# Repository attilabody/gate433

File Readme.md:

# Shared parking space access controller

## Features

Gate433 uses cheap, standard (and insecure) gate opener remotes operating on 433 MHz to control entry and exit of vehicles allowed to acces the parking area.

Each gate opener supposed to be assigned to one vehicle and has unique code. The main purpose of it is to make unfair usage of the parking as inconvinient as possible using commodity gate opener remotes.

Features list:

* 1024 possible remote codes
* Position of each vehicle (inside, outside, unknown) is remembered. Gate opening will be denied for unexpected movements (e.g vehicle which is already inside tries to enter again)
* Access time limits by direction can be set independently for any vehicle (e.g can enter Monday to Friday from 08:30 to 17:00, can leave Monday to Friday from 08:30 to 17:30)
* Vehicle database snd device configuration stored in EEPROM
* Log stored on SD card
* Database changes can be imported from SD card
* Exceptional days (e.g. National holydays) database on SD card
* Automatic DST handling
* Simple command line interpreter on serial for database manipulation, date/time setting, log manipulation and temperature query

## Hardware

There are two versions of the hardware: Original version used Arduino Nano as central component. It is obsoleted by the newer version based on a popular STM32F103C8T6 based minimal board widely known as BluePill. It's actually cheaper on eBay or Aliexpress than the total cost of the components it contains.

Both versions ar using two inputs (usually coming from inductive loop detectors) in addition to the RF signal to decide if a vehicke intends to enter or exit. A pair of tricolor traffic lights provide feedback for drivers.

Both versions have 6 opto-isolated open drain output for 12V LED traffic lights,one opto-isolated open collector output for gate opening and two opto-isolated input for inductive loop detectors.

Second iteration have three extra features compared to the first:

* WiFi to serial bridge for wireless communication
* Rotary encoder driven simpe user interface (yet to be implemented in the firmware)
* 3D printable case modelled in FreeCAD

Prototype of STM32 based version

## Firmware

Arduino Nano based firware was built on Arduino framework using Sloeber Arduino IDE. Source files persist in folders named "gatekeeper", "common" and "libs".  
STM32 version is completely separated as it is based on STM32Cube framework. STM32 sources are placed in "gatekeeper-stm32" and "stm32goodies" folder.

## Schematics and PCB

Arduino based first version hardware developed using proprietrary Eagle free version, and obsoleted by STM32 version but schematics of the [mainboard](docs/V1_mainboard.pdf) and the [IO panel](docs/V1_extio.pdf) are still available for reference.

As mentioned above, hardware of STM32 version designed using KiCAD. The complete EDA project is available in the hardware/STM32 folder. Here are the [schematics](docs/bluepill.pdf) in PDF for easier access.

PCB design for STM32 bsed version

Assembled STM32 panel with modules installed

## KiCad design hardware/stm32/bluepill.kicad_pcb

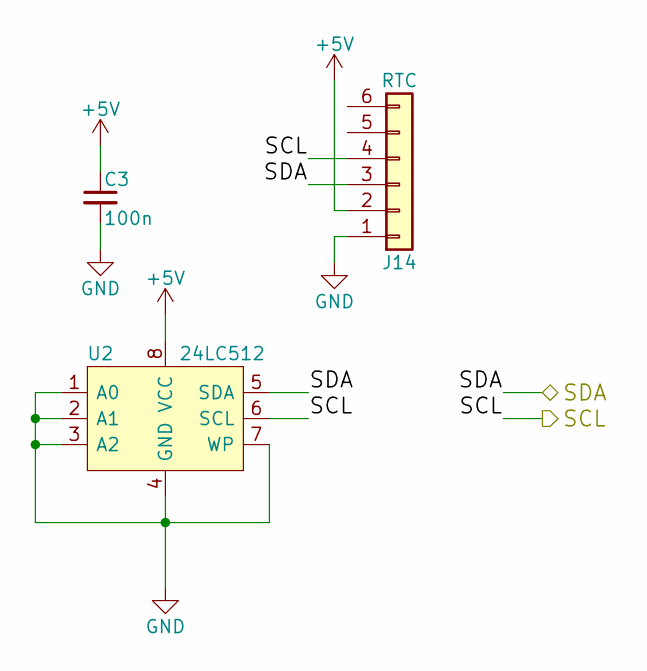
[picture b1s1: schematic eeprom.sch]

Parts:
C3: 100n; C_0805
J14: RTC; Pin_Header_Straight_1x06_Pitch2.54mm
U2: 24LC512; DIP-8_W7.62mm_LongPads

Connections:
+5V: C3.1, J14.2, U2.8 (VCC); also elsewhere on the board
/EEPROM/SCL: J14.4, U2.6 (SCL); also elsewhere on the board
/EEPROM/SDA: J14.3, U2.5 (SDA); also elsewhere on the board
GND: C3.2, J14.1, U2.1 (A0), U2.2 (A1), U2.3 (A2), U2.4 (GND), U2.7 (WP); also elsewhere on the board

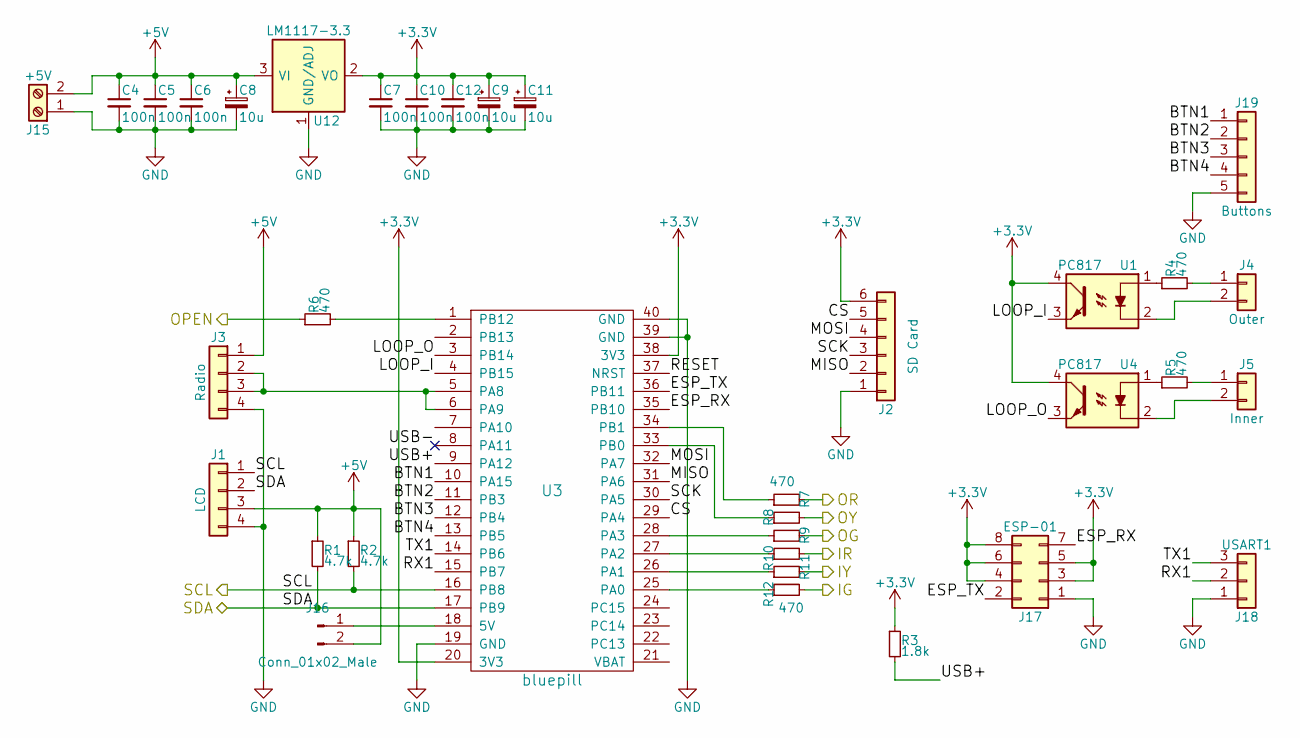
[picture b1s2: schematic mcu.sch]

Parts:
C4, C5, C6, C7, C10, C12: 100n; C_0805
C8, C9, C11: 10u; CP_Tantalum_Case-A_EIA-3216-18_Reflow
J1: LCD; Pin_Header_Straight_1x04_Pitch2.54mm
J2: SD Card; Pin_Header_Straight_1x06_Pitch2.54mm
J3: Radio; Pin_Header_Straight_1x04_Pitch2.54mm
J4: Outer; Pin_Header_Straight_1x02_Pitch2.54mm
J5: Inner; Pin_Header_Straight_1x02_Pitch2.54mm
J15: +5V; TerminalBlock_bornier-2_P5.08mm
J16: Conn_01x02_Male; Pin_Header_Straight_1x02_Pitch2.54mm
J17: ESP-01; Socket_Strip_Straight_2x04_Pitch2.54mm
J18: USART1; Pin_Header_Straight_1x03_Pitch2.54mm
J19: Buttons; Pin_Header_Straight_1x05_Pitch2.54mm
R1, R2: 4.7k; R_0603_HandSoldering
R3: 1.8k; R_0603_HandSoldering
R4, R5, R6, R7, R8, R9, R10, R11, R12: 470; R_0603_HandSoldering
U1, U4: PC817; DIP-4_W7.62mm_LongPads
U3: bluepill
U12: LM1117-3.3; SOT-223

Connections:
+3V3: C7.1, C9.1, C10.1, C11.1, C12.1, J2.6, J17.3, J17.4, J17.5, J17.6, J17.8, R3.1, U1.4, U3.20 (3V3), U3.38 (3V3), U4.4, U12.2 (VO), U12.4 (VO); also elsewhere on the board
+5V: C4.1, C5.1, C6.1, C8.1, J1.3, J3.1, J15.2, J16.2, R1.1, R2.1, U12.3 (VI); also elsewhere on the board
/EEPROM/SCL: J1.1, R2.2, U3.16 (PB8); also elsewhere on the board
/EEPROM/SDA: J1.2, R1.2, U3.17 (PB9); also elsewhere on the board
/MCU/BTN1: J19.1, U3.10 (PA15)
/MCU/BTN2: J19.2, U3.11 (PB3)
/MCU/BTN3: J19.3, U3.12 (PB4)
/MCU/BTN4: J19.4, U3.13 (PB5)
/MCU/CS: J2.5, U3.29 (PA4)
/MCU/ESP_RX: J17.7, U3.35 (PB10)
/MCU/ESP_TX: J17.2, U3.36 (PB11)
/MCU/IG: R12.2; also elsewhere on the board
/MCU/IR: R10.2; also elsewhere on the board
/MCU/IY: R11.2; also elsewhere on the board
/MCU/LOOP_I: U1.3, U3.4 (PB15)
/MCU/LOOP_O: U3.3 (PB14), U4.3
/MCU/MISO: J2.2, U3.31 (PA6)
/MCU/MOSI: J2.4, U3.32 (PA7)
/MCU/OG: R9.2; also elsewhere on the board
/MCU/OPEN: R6.1; also elsewhere on the board
/MCU/OR: R7.2; also elsewhere on the board
/MCU/OY: R8.2; also elsewhere on the board
/MCU/RX1: J18.2, U3.15 (PB7)
/MCU/SCK: J2.3, U3.30 (PA5)
/MCU/TX1: J18.3, U3.14 (PB6)
/MCU/USB+: R3.2, U3.9 (PA12)
GND: C4.2, C5.2, C6.2, C7.2, C8.2, C9.2, C10.2, C11.2, C12.2, J1.4, J2.1, J3.4, J15.1, J17.1, J18.1, J19.5, U3.19 (GND), U3.39 (GND), U3.40 (GND), U12.1 (GND/ADJ); also elsewhere on the board
unnamed: J3.2, J3.3, U3.5 (PA8), U3.6 (PA9)
unnamed: J4.1, R4.2
unnamed: J4.2, U1.2
unnamed: J5.1, R5.2
unnamed: J5.2, U4.2
unnamed: J16.1, U3.18 (5V)
unnamed: R4.1, U1.1
unnamed: R5.1, U4.1
unnamed: R6.2, U3.1 (PB12)
unnamed: R7.1, U3.34 (PB1)
unnamed: R8.1, U3.33 (PB0)
unnamed: R9.1, U3.28 (PA3)
unnamed: R10.1, U3.27 (PA2)
unnamed: R11.1, U3.26 (PA1)
unnamed: R12.1, U3.25 (PA0)

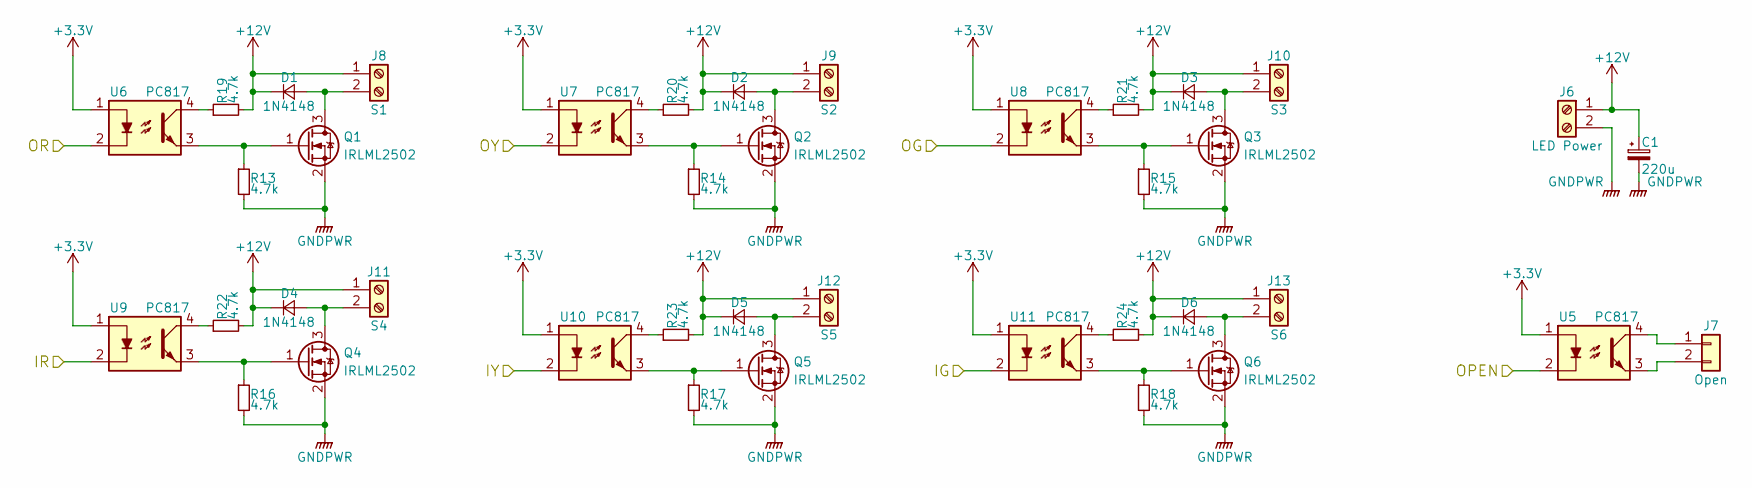
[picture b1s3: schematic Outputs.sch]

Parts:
C1: 220u; CP_Radial_D10.0mm_P3.50mm
D1, D2, D3, D4, D5, D6: 1N4148; D_MiniMELF
J6: LED Power; TerminalBlock_bornier-2_P5.08mm
J7: Open; JST_EH_B02B-EH-A_02x2.50mm_Straight
J8: S1; TerminalBlock_bornier-2_P5.08mm
J9: S2; TerminalBlock_bornier-2_P5.08mm
J10: S3; TerminalBlock_bornier-2_P5.08mm
J11: S4; TerminalBlock_bornier-2_P5.08mm
J12: S5; TerminalBlock_bornier-2_P5.08mm
J13: S6; TerminalBlock_bornier-2_P5.08mm
Q1, Q2, Q3, Q4, Q5, Q6: IRLML2502; SOT-23
R13, R14, R15, R16, R17, R18, R19, R20, R21, R22, R23, R24: 4.7k; R_0603_HandSoldering
U5: PC817; DIP-4_W7.62mm_LongPads
U6, U7, U8, U9, U10, U11: PC817; DIP-4_W7.62mm

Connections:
+3V3: U5.1, U6.1, U7.1, U8.1, U9.1, U10.1, U11.1; also elsewhere on the board
+12V: C1.1, D1.1 (K), D2.1 (K), D3.1 (K), D4.1 (K), D5.1 (K), D6.1 (K), J6.1, J8.1, J9.1, J10.1, J11.1, J12.1, J13.1, R19.2, R20.2, R21.2, R22.2, R23.2, R24.2
/MCU/IG: U11.2; also elsewhere on the board
/MCU/IR: U9.2; also elsewhere on the board
/MCU/IY: U10.2; also elsewhere on the board
/MCU/OG: U8.2; also elsewhere on the board
/MCU/OPEN: U5.2; also elsewhere on the board
/MCU/OR: U6.2; also elsewhere on the board
/MCU/OY: U7.2; also elsewhere on the board
GNDPWR: C1.2, J6.2, Q1.2 (S), Q2.2 (S), Q3.2 (S), Q4.2 (S), Q5.2 (S), Q6.2 (S), R13.2, R14.2, R15.2, R16.2, R17.2, R18.2
unnamed: D1.2 (A), J8.2, Q1.3 (D)
unnamed: D2.2 (A), J9.2, Q2.3 (D)
unnamed: D3.2 (A), J10.2, Q3.3 (D)
unnamed: D4.2 (A), J11.2, Q4.3 (D)
unnamed: D5.2 (A), J12.2, Q5.3 (D)
unnamed: D6.2 (A), J13.2, Q6.3 (D)
unnamed: J7.1, U5.4
unnamed: J7.2, U5.3
unnamed: Q1.1 (G), R13.1, U6.3
unnamed: Q2.1 (G), R14.1, U7.3
unnamed: Q3.1 (G), R15.1, U8.3
unnamed: Q4.1 (G), R16.1, U9.3
unnamed: Q5.1 (G), R17.1, U10.3
unnamed: Q6.1 (G), R18.1, U11.3
unnamed: R19.1, U6.4
unnamed: R20.1, U7.4
unnamed: R21.1, U8.4
unnamed: R22.1, U9.4
unnamed: R23.1, U10.4
unnamed: R24.1, U11.4

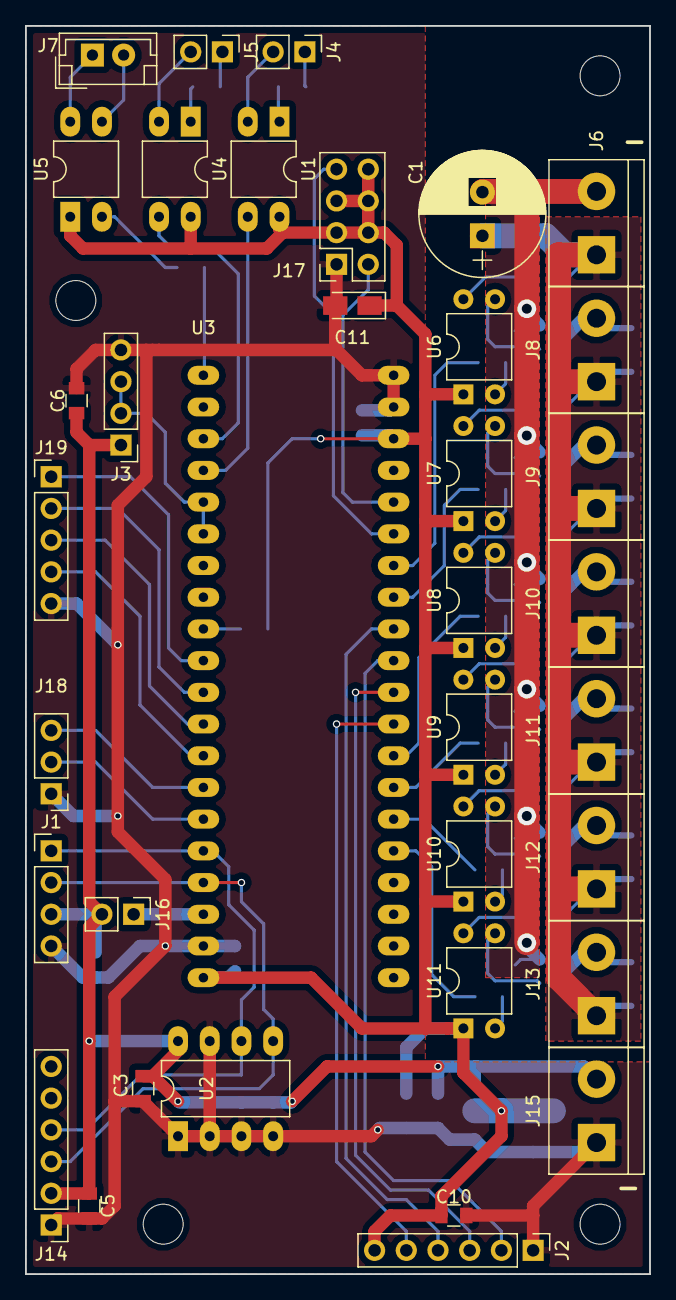
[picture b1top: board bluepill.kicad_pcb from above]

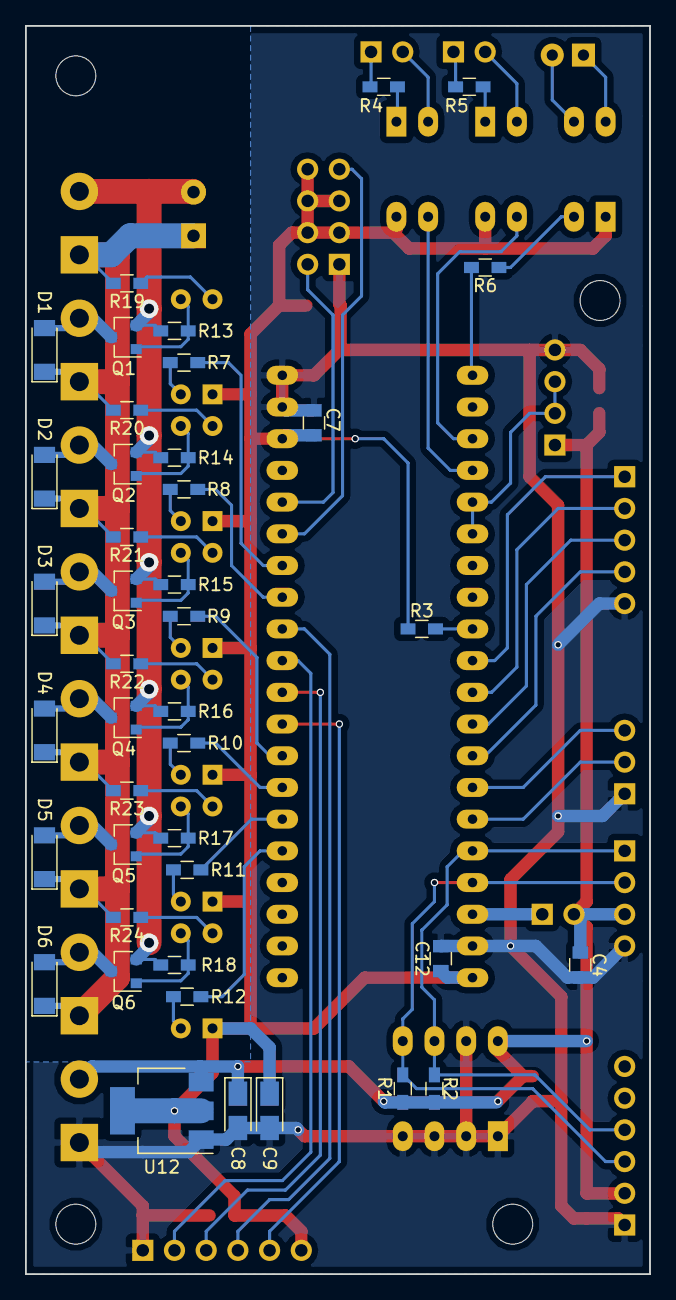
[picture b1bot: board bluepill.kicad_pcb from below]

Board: 2 copper layers, 50.0 x 100.0 mm, 78 parts (42 on the bottom side), 64 nets.

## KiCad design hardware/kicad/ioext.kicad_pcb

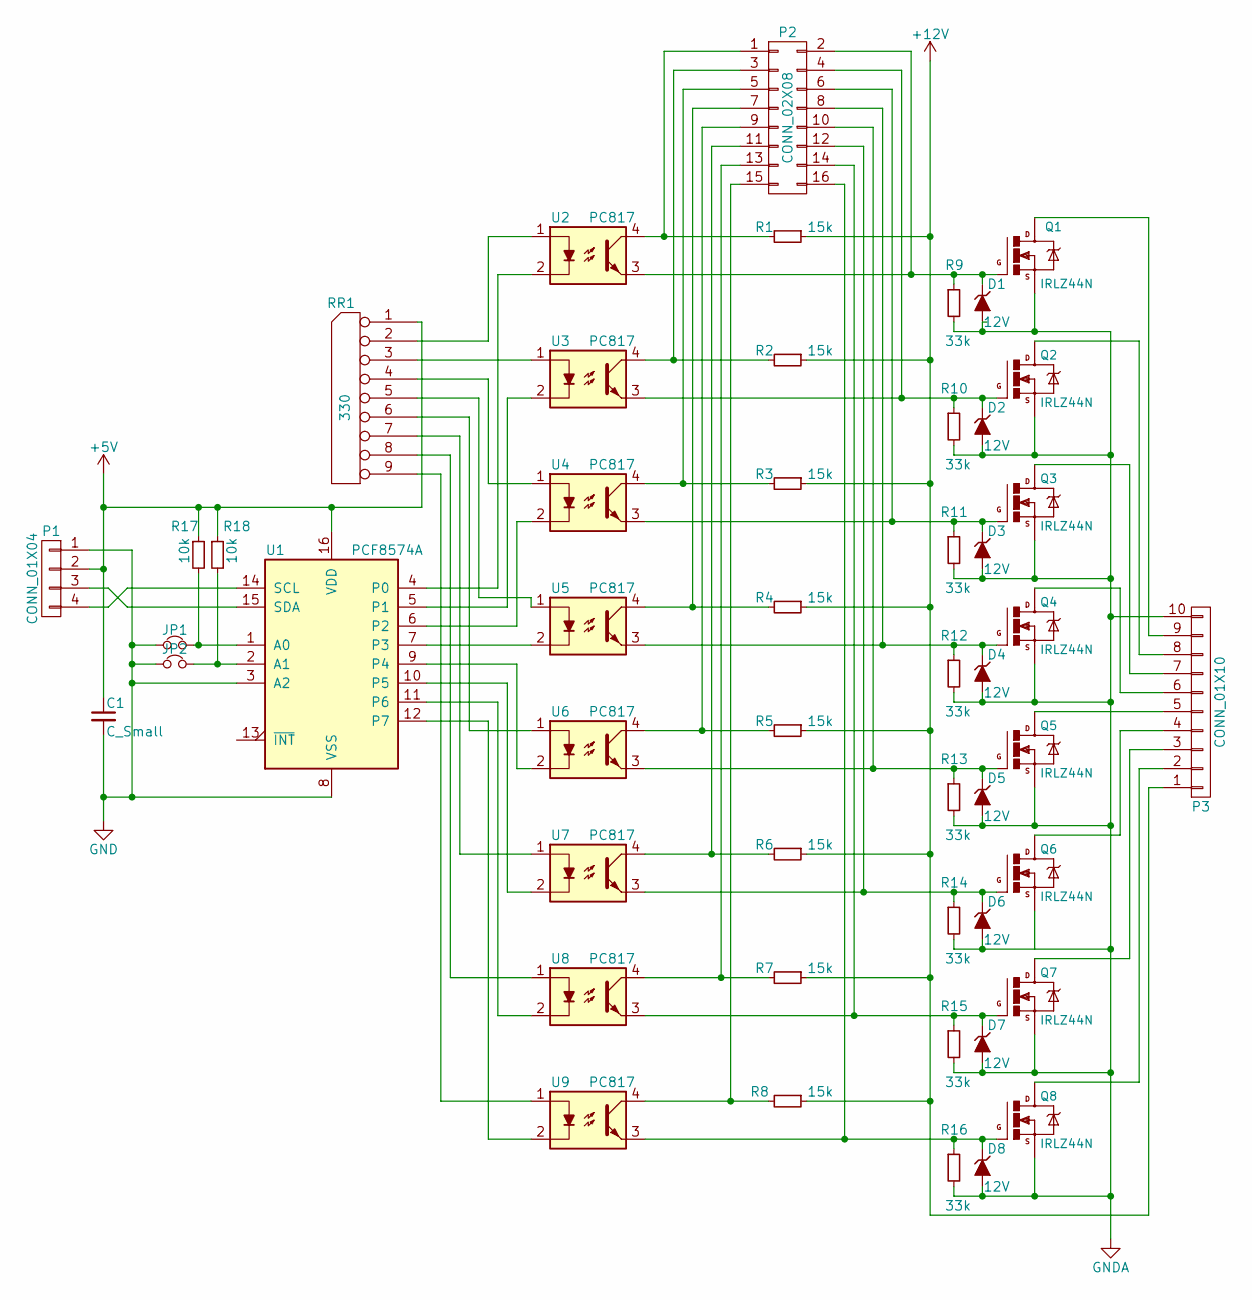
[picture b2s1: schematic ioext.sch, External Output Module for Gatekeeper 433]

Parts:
C1: C_Small; C_0603_HandSoldering
D1, D2, D3, D4, D5, D6, D7, D8: 12V; SOD80C
JP1, JP2: Jumper_NC_Small; Pin_Header_Straight_1x02
P1: CONN_01X04; Pin_Header_Straight_1x04
P2: CONN_02X08; Pin_Header_Straight_2x08
P3: CONN_01X10; W237-10P
Q1, Q2, Q3, Q4, Q5, Q6, Q7, Q8: IRLZ44N; TO-220_Neutral123_Vertical
R1, R2, R3, R4, R5, R6, R7, R8: 15k; R_0603_HandSoldering
R9, R10, R11, R12, R13, R14, R15, R16: 33k; R_0603_HandSoldering
R17, R18: 10k; R_0603_HandSoldering
RR1: 330; Resistor_Array_SIP8
U1: PCF8574A; DIP-16_W7.62mm_LongPads
U2, U3, U4, U5, U6, U7, U8, U9: PC817; DIP-4_W7.62mm

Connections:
+5V: C1.1, P1.2, R17.1, R18.1, RR1.1 (COM), U1.16 (VDD)
+12V: P3.1, R1.1, R2.1, R3.1, R4.1, R5.1, R6.1, R7.1, R8.1
GND: C1.2, JP1.1, JP2.1, P1.1, U1.3 (A2), U1.8 (VSS)
GNDA: D1.2 (A), D2.2 (A), D3.2 (A), D4.2 (A), D5.2 (A), D6.2 (A), D7.2 (A), D8.2 (A), P3.10, Q1.3 (S), Q2.3 (S), Q3.3 (S), Q4.3 (S), Q5.3 (S), Q7.3 (S), Q8.3 (S), R9.2, R10.2, R11.2, R12.2, R13.2, R14.2, R15.2, R16.2
unnamed: D1.1 (K), P2.2, Q1.1 (G), R9.1, U2.3
unnamed: D2.1 (K), P2.4, Q2.1 (G), R10.1, U3.3
unnamed: D3.1 (K), P2.6, Q3.1 (G), R11.1, U4.3
unnamed: D4.1 (K), P2.8, Q4.1 (G), R12.1, U5.3
unnamed: D5.1 (K), P2.10, Q5.1 (G), R13.1, U6.3
unnamed: D6.1 (K), P2.12, Q6.1 (G), R14.1, U7.3
unnamed: D7.1 (K), P2.14, Q7.1 (G), R15.1, U8.3
unnamed: D8.1 (K), P2.16, Q8.1 (G), R16.1, U9.3
unnamed: JP1.2, R17.2, U1.1 (A0)
unnamed: JP2.2, R18.2, U1.2 (A1)
unnamed: P1.3, U1.15 (SDA)
unnamed: P1.4, U1.14 (SCL)
unnamed: P2.1, R1.2, U2.4
unnamed: P2.3, R2.2, U3.4
unnamed: P2.5, R3.2, U4.4
unnamed: P2.7, R4.2, U5.4
unnamed: P2.9, R5.2, U6.4
unnamed: P2.11, R6.2, U7.4
unnamed: P2.13, R7.2, U8.4
unnamed: P2.15, R8.2, U9.4
unnamed: P3.2, Q8.2 (D)
unnamed: P3.3, Q7.2 (D)
unnamed: P3.4, Q6.2 (D)
unnamed: P3.5, Q5.2 (D)
unnamed: P3.6, Q4.2 (D)
unnamed: P3.7, Q3.2 (D)
unnamed: P3.8, Q2.2 (D)
unnamed: P3.9, Q1.2 (D)
unnamed: RR1.2, U2.1
unnamed: RR1.3, U3.1
unnamed: RR1.4, U4.1
unnamed: RR1.5, U5.1
unnamed: RR1.6, U6.1
unnamed: RR1.7, U7.1
unnamed: RR1.8, U8.1
unnamed: RR1.9, U9.1
unnamed: U1.4 (P0), U2.2
unnamed: U1.5 (P1), U3.2
unnamed: U1.6 (P2), U4.2
unnamed: U1.7 (P3), U5.2
unnamed: U1.9 (P4), U6.2
unnamed: U1.10 (P5), U7.2
unnamed: U1.11 (P6), U8.2
unnamed: U1.12 (P7), U9.2

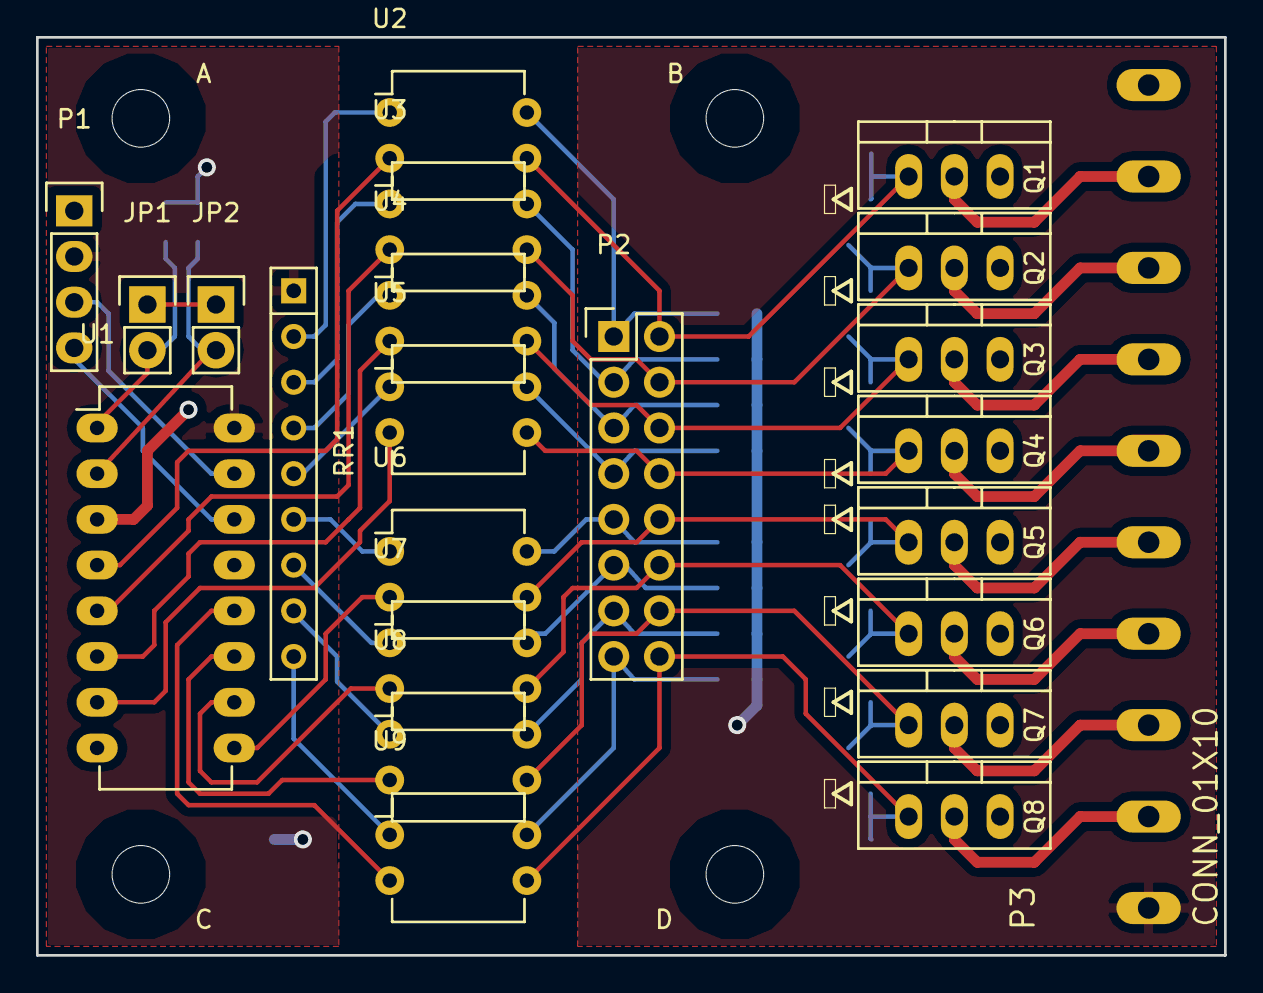
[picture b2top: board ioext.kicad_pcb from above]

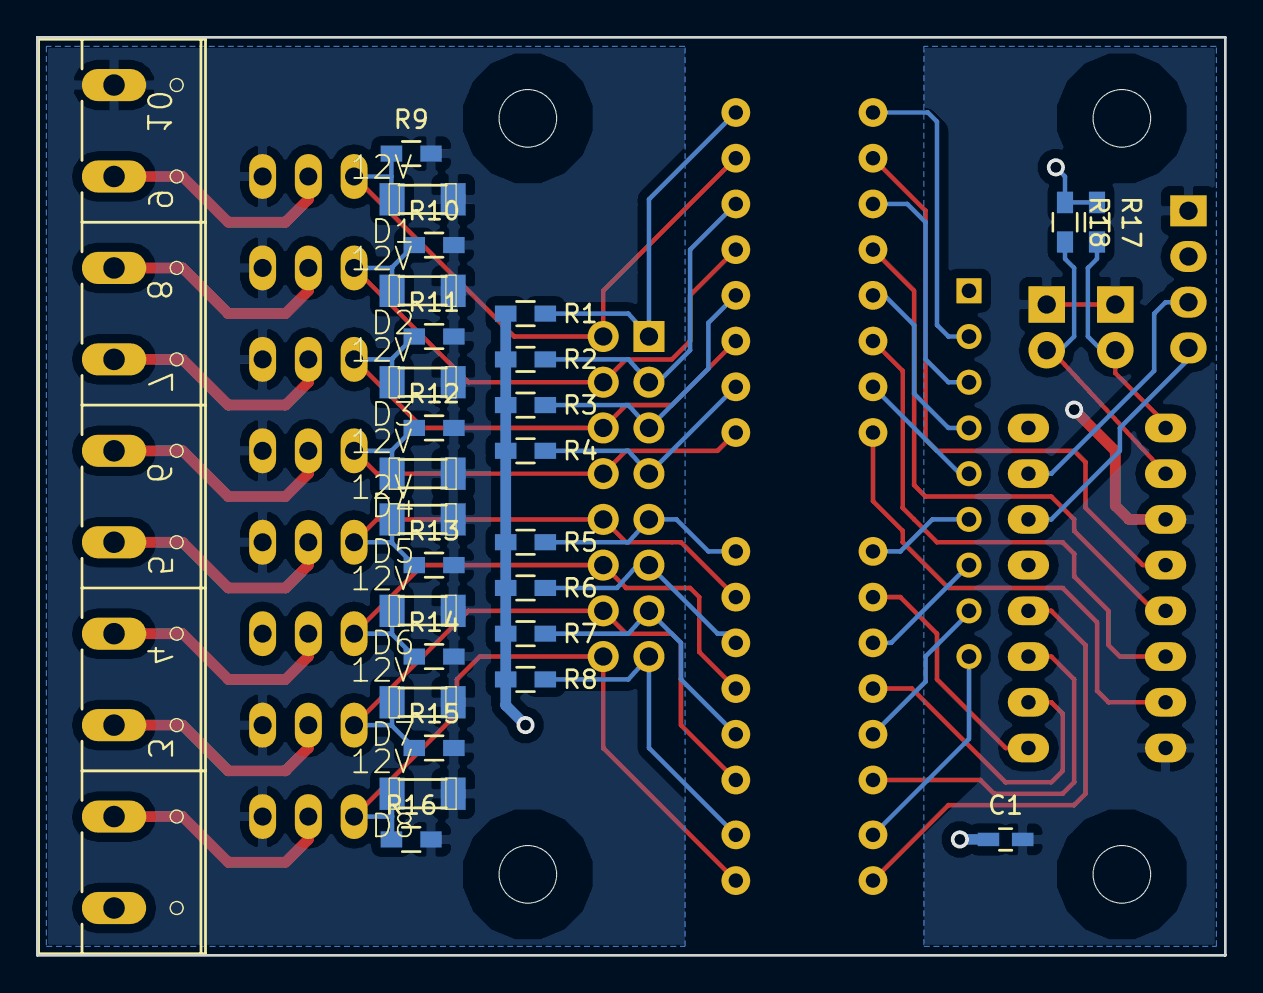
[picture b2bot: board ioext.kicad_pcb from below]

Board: 2 copper layers, 66.0 x 51.0 mm, 54 parts (27 on the bottom side), 48 nets.

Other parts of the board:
A: MountingHole_3.2mm_M3
B: MountingHole_3.2mm_M3
C: MountingHole_3.2mm_M3
D: MountingHole_3.2mm_M3

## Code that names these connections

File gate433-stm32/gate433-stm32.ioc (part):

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Mcu.Name=STM32F103C(8-B)Tx
Mcu.Package=LQFP48
Mcu.UserName=STM32F103C8Tx
PA0-WKUP.GPIOParameters=GPIO_ModeDefaultPP,GPIO_Speed
PA0-WKUP.GPIO_ModeDefaultPP=GPIO_MODE_AF_OD
PA0-WKUP.GPIO_Speed=GPIO_SPEED_FREQ_LOW
PA0-WKUP.Signal=S_TIM2_CH1_ETR
PA1.GPIOParameters=GPIO_ModeDefaultPP,GPIO_Speed
PA1.GPIO_ModeDefaultPP=GPIO_MODE_AF_OD
PA1.GPIO_Speed=GPIO_SPEED_FREQ_LOW
PA1.Signal=S_TIM2_CH2
PA13.Mode=Serial_Wire
PA13.Signal=SYS_JTMS-SWDIO
PA14.Mode=Serial_Wire
PA14.Signal=SYS_JTCK-SWCLK
PA15.GPIOParameters=GPIO_PuPd,GPIO_Label,GPIO_ModeDefaultEXTI
PA15.GPIO_Label=BTN_CLK
PA15.GPIO_ModeDefaultEXTI=GPIO_MODE_IT_RISING_FALLING
PA15.GPIO_PuPd=GPIO_PULLUP
PA15.Signal=GPXTI15
PA2.GPIOParameters=GPIO_ModeDefaultPP,GPIO_Speed
PA2.GPIO_ModeDefaultPP=GPIO_MODE_AF_OD
PA2.GPIO_Speed=GPIO_SPEED_FREQ_LOW
PA2.Signal=S_TIM2_CH3
PA3.GPIOParameters=GPIO_ModeDefaultPP,GPIO_Speed
PA3.GPIO_ModeDefaultPP=GPIO_MODE_AF_OD
PA3.GPIO_Speed=GPIO_SPEED_FREQ_LOW
PA3.Signal=S_TIM2_CH4
PA4.GPIOParameters=GPIO_Speed,PinState,GPIO_Label
PA4.GPIO_Label=SD_CS
PA4.GPIO_Speed=GPIO_SPEED_FREQ_MEDIUM
PA4.PinState=GPIO_PIN_SET
PA4.Signal=GPIO_Output
PA5.Mode=Full_Duplex_Master
PA5.Signal=SPI1_SCK
PA6.Mode=Full_Duplex_Master
PA6.Signal=SPI1_MISO
PA7.Mode=Full_Duplex_Master
PA7.Signal=SPI1_MOSI
PA8.Signal=S_TIM1_CH1
PA9.Signal=S_TIM1_CH2
PB0.GPIOParameters=GPIO_ModeDefaultPP,GPIO_Speed
PB0.GPIO_ModeDefaultPP=GPIO_MODE_AF_OD
PB0.GPIO_Speed=GPIO_SPEED_FREQ_LOW
PB0.Signal=S_TIM3_CH3
PB1.GPIOParameters=GPIO_ModeDefaultPP,GPIO_Speed
PB1.GPIO_ModeDefaultPP=GPIO_MODE_AF_OD
PB1.GPIO_Speed=GPIO_SPEED_FREQ_LOW
PB1.Signal=S_TIM3_CH4
PB10.Mode=Asynchronous
PB10.Signal=USART3_TX
PB11.Mode=Asynchronous
PB11.Signal=USART3_RX
PB12.GPIOParameters=PinState,GPIO_Label,GPIO_ModeDefaultOutputPP
PB12.GPIO_Label=OPEN
PB12.GPIO_ModeDefaultOutputPP=GPIO_MODE_OUTPUT_OD
PB12.PinState=GPIO_PIN_SET
PB12.Signal=GPIO_Output
PB14.GPIOParameters=GPIO_PuPd,GPIO_Label
PB14.GPIO_Label=LOOP_O
PB14.GPIO_PuPd=GPIO_PULLDOWN
PB14.Signal=GPIO_Input
PB15.GPIOParameters=GPIO_PuPd,GPIO_Label
PB15.GPIO_Label=LOOP_I
PB15.GPIO_PuPd=GPIO_PULLDOWN
PB15.Signal=GPIO_Input
PB3.GPIOParameters=GPIO_PuPd,GPIO_Label
PB3.GPIO_Label=BTN_DATA
PB3.GPIO_PuPd=GPIO_PULLUP
PB3.Signal=GPIO_Input
PB4.GPIOParameters=GPIO_PuPd,GPIO_Label,GPIO_ModeDefaultEXTI
PB4.GPIO_Label=BTN_SW
PB4.GPIO_ModeDefaultEXTI=GPIO_MODE_IT_RISING_FALLING
PB4.GPIO_PuPd=GPIO_PULLUP
PB4.Signal=GPXTI4
PB5.GPIOParameters=PinState,GPIO_Label
PB5.GPIO_Label=BTN_PLUS
PB5.PinState=GPIO_PIN_SET
PB5.Signal=GPIO_Output
PB6.Mode=Asynchronous
PB6.Signal=USART1_TX
PB7.Mode=Asynchronous
PB7.Signal=USART1_RX
PB8.Mode=I2C
PB8.Signal=I2C1_SCL
PB9.Mode=I2C
PB9.Signal=I2C1_SDA
PC13-TAMPER-RTC.GPIOParameters=PinState
PC13-TAMPER-RTC.PinState=GPIO_PIN_SET
PC13-TAMPER-RTC.Signal=GPIO_Output
PC14-OSC32_IN.Mode=LSE-External-Oscillator
PC14-OSC32_IN.Signal=RCC_OSC32_IN
PC15-OSC32_OUT.Mode=LSE-External-Oscillator
PC15-OSC32_OUT.Signal=RCC_OSC32_OUT
PD0-OSC_IN.Mode=HSE-External-Oscillator
PD0-OSC_IN.Signal=RCC_OSC_IN
PD1-OSC_OUT.Mode=HSE-External-Oscillator
PD1-OSC_OUT.Signal=RCC_OSC_OUT
RCC.SYSCLKFreq_VALUE=72000000
RCC.SYSCLKSource=RCC_SYSCLKSOURCE_PLLCLK
board=gate433-stm32

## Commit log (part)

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2015-09-27 interrupt driven listing
2015-09-29 Using timer0 compare a interrupt to afterglow LED
2015-10-03 globals
2015-10-03 Squashed 'libs/Time/' content from commit a7cc326
    git-subtree-dir: libs/Time
    git-subtree-split: a7cc3261f91af37ca3d8c8e192fa4030445178e7
2015-10-05 gatedemo_test created
2015-10-05 timing.txt added
2015-10-06 faking
2015-10-06 VS test session fixes
2015-10-07 ignoring *.d
2015-10-07 corrected high/low drive
2015-10-07 variable rename (curmicro->now)
2015-10-09 using local static variable tor data shifting to improve locking in ISR
2015-10-10 tuning
2015-10-10 stats
2015-10-11 cleaning up && fixing timing
2015-10-14 Squashed 'libs/ds3231/' content from commit 9ea45be
    git-subtree-dir: libs/ds3231
    git-subtree-split: 9ea45be66f0b5374a520a9630fde649175f5f068
2015-10-15 ds3231 progress
2015-10-16 Squashed 'libs/Adafruit-GFX-Library/' content from commit 0acee33
    git-subtree-dir: libs/Adafruit-GFX-Library
    git-subtree-split: 0acee33cfe8b500c5a2a1c4f29913746936b53ba
2015-10-16 Squashed 'libs/TFTLCDplus-Library/' content from commit 82b13b3
    git-subtree-dir: libs/TFTLCDplus-Library
    git-subtree-split: 82b13b39e15d263f9cafa06388a885511f3b6400
2015-10-17 DS3231
2015-10-17 renaming madness
2015-10-17 demo
2015-10-18 making it compile again (step 1)
2015-10-21 getintparam bugfix
2015-10-22 GET SET SETF SHOW implemented
2015-10-24 buttons
2015-10-25 refactor for displaying communication
2015-10-27 moving repetition limit from loop() to ISR, explicitly sized types ((u)int_#_t)
2015-10-28 BAUDRATE TO 38400
2015-10-29 renamint interface.cpp to interface_main.cpp
2015-10-29 gatehandler beginnings + common interface code
2015-10-30 common functions moved out
2015-10-30 testing 1,2,3
2015-10-31 remote recording ready.
2015-11-01 getintparam cleanup, dbrecord parsing
2015-11-03 test fixed to debug brain demaged remote control fix
2015-11-06 changing types (to explicitly sized)
2015-11-08 separated info & status file step 1
2015-11-08 separated info & status file step 2
2015-11-09 command parsing bugfix
2015-11-09 excluding lib examples
2015-11-12 gatelogic: database handler class proto
2015-11-12 gatelogic: database handler progress
2015-11-13 gatelogic_test
2015-11-15 fakelibs reorg
2015-11-17 gatelogic progress
2015-11-27 boardtest added
2015-12-06 merging subtreerepos.txt content from gatelogic
2015-12-09 inductiveloop progress (get rid of config.h dependency)
2015-12-09 LiquidCrystal_I2C library added
2015-12-10 common added to boardtest
2015-12-10 boardtest working
2015-12-12 boardtest set time
2015-12-13 database related stuff moved to common
2015-12-14 making gatelogic_test to compile
2015-12-17 boardtest: component ifdefs
2015-12-18 added executeable permission to python scripts
2015-12-18 RF signal decoding parts moved to common
2015-12-18 lamp class seems to be working
2015-12-19 removing some debris
2015-12-21 inductiveloop tuning
2015-12-23 failstats to decode433
2015-12-29 assembling
2015-12-30 trafficlights_test: LCD
2015-12-31 trafficlights_test: code from serial
2016-01-01 trafficlights_test: testing && fixing session results
2016-01-01 project renames gatelogic -> gatekeeper trafficlights_test -> testbed
2016-01-01 testbed progress (set serial command)
2016-01-03 boardtest compile fix && remove trafficlights testing
2016-01-03 very WIP
2016-01-04 thindb
2016-01-05 LCD bug (constructor &) fixed.
2016-01-05 using PCF8574 instead of arduino I/O pins for relay output
2016-01-06 hybriddb first checkin (expect shore edges)
2016-01-07 added streaming library to libs
2016-01-08 i2c_eeprom class
2016-01-09 flashdb fixing
2016-01-10 minor boardtest improvements
2016-01-11 minor boardtst improvements
2016-01-11 gatelogic.cpp renamed to gatekeeper
2016-01-18 gatelogic_test renamed to gatekeeper_test
2016-01-21 relaxed mode (for "beta")
2016-01-24 testbed compile fix
2016-01-27 date exception handling
2016-01-27 testbed reorg
2016-01-27 logging v2
2016-01-28 boardtest lcd reorg
2016-01-29 GOD mode (emergency) code handling
2016-01-30 trafficlights instance moved into gatehandler (was global)
2016-01-30 gate relay handled by outputpin class eliminate m_[hig|low]value from outputpin
2016-01-31 gatekeeper log filling on receive bugfix
2016-02-02 importdb (creates simpledb file form owners.txt and tenants.txt)
2016-02-02 boardtest print free memory to LCD at startup
2016-02-02 preparing relay output gpio abstraction
2016-02-02 gatekeeper: cs command (clean ststuses)
2016-02-04 refactoring decoder code handling
2016-02-04 hybintdb (SD+internal eeprom) gatekeeper: additiona logging before and after DB update
2016-02-12 log dump watchdog update
2016-02-13 Squashed 'libs/TimerOne/' content from commit 9790739
    git-subtree-dir: libs/TimerOne
    git-subtree-split: 979073973b09aa5d084224fe351e7b46ed358f6e
2016-02-13 gk_simple: logging
2016-02-13 loadtest: initial commit
2016-02-13 gk_simple: ID should be between 4 and 1019
2016-02-13 gk_simple: handle lights
2016-02-13 gk_simple
2016-02-13 gk_simple: added valid date/time to log
2016-02-13 gk_simple: Fixing traffic lights pins (inside<->outside)
2016-02-13 codereader: prettier print
2016-02-13 gk_simple: VERBOSE
2016-02-13 codereader: initial commit
2016-02-13 codereader: adding SD log
2016-02-13 boardtest: reverse 433 decoding switched on
2016-02-13 libs/I2C: added write16 and read16 functions
2016-02-14 syncing to markers (gate433 related)
2016-02-15 coredeader: USE_SDCARD && dummylogwriter
2016-02-16 codereader: RTC handling
2016-02-16 common: decode433 tuning
2016-02-17 gk_simple using libs/I2C
    ds3231 using libs/I2C
2016-02-17 boardtest: stress testintg I2C; switch off reversed RF bit order gatekeeper: switch off reversed RF bit order
2016-02-17 libs/I2C: write16 bugfix
2016-02-18 libs/PCF8574: Wire->I2c testbed: i2cioexttest
2016-02-18 boardtest: using new I2C lib based devices
2016-02-18 gk_simple: db import (to EEPROM)
2016-02-21 boardtest: incoming code logging
2016-02-27 gk_simple: remote controller registration restrictions effective.
2016-03-01 gk_simple: inductive loop aborts traffic light delay
2016-03-05 gatekeeper: + I2C lib; + gatehandler invalid state protection; codereader: Enable I2C lib loadtest: include path fix (+common)
2016-03-06 createdb: gitignore case issue fix
2016-03-13 gk_simple: Switching green to red when induction loop changes during passage, holding it until there's no car on either loops.
2016-03-15 * optimization; + updateloopstatuscalc
2016-03-17 gk_simple: eepromdb -> i2cdb
2016-03-18 loadtest: rf code sending (send, sweep commands)
2016-03-23 importdb fix and optimalization
2016-03-23 DS3231Test
2016-03-25 * DS3231 full static class + DST capability moved to DS3231_DST + class DS3231 function calls replaced to DS3231_DST calls * gk_simple EEPROM.h fix
2016-03-27 gatekeeper: datetime update over-optimization bug fix
2016-03-28 libs/DS3231: manual-optimizing get & set for size boardtest: use DS3231 class for date&time
2016-03-28 + auto wday in DS3231; - parsedatetime wday;
2016-04-01 + decode433 stop watch (>last cycle time) after 12 bit
2016-04-02 Eclipse Arduino plugin V3 conversion
2016-04-03 loadtest: Build fix (project settings)
2016-04-05 createdb: - backing up DB.TXT (to DB.BAK) on import - ignoring backup files in git
2016-04-08 gatekeeper: - trafficlights is a global now (as loop, db, etc) - switching on and off lights at restart - time invalid status appears on the display
2016-04-09 gatekeeper: moved output classes to common
2016-04-14 GPIO: detaching outputpin from g_outputs (prepare moving of gate open signal to a different output port)
2016-04-14 libs/i2c_eeprom: I2C error handling
2016-04-17 barereader: decode433 (from common) added
2016-04-17 barereader: LED eye-candy common/decode433: counting overruns (up to 255)
2016-04-21 freqcntr: first functional version
2016-04-22 gatekeeper: re-think WARN
2016-04-29 Eclipse blah
2016-05-14 freqcntr: I2C LCD feature switch
2016-06-05 hardware: schematics and board added
2016-06-06 extio board
2016-06-08 mainboard SMD update
2016-06-08 extio connector fix
2016-06-11 extio C1 to SMD
2016-06-12 kicad-ioext: wiring
2016-06-12 hardware: eagle files moved from hardware/ to hardware/eagle/ kicad files moved from kicad/ to harware/kicad/ .gitignore modified to follow changes
2016-06-16 ExtIO A0..A1: jmp1..jmp2
2016-06-19 hardware/kicad ioext: use 3x jumper block insterad of inidividual jumpers
2016-07-16 gatekeeper: CLR by SD
2016-07-24 gatekeeper: enable watchdog timer (!!!uno bootloader required!!!) ddb && dl: data lines start with ">" instead of ":" log dump: additional parameter to truncate after dump
2017-05-11 Logger Auth messages fix for missing btn parameter
2017-05-11 eclipse preferences
2017-06-07 gatekeeper converted to sloeber 4.1 IDE
2018-01-11 bluepill: basic timer setup for semaphore outputs
2018-01-13 bluepill: timer interrupts for RF activated
2018-01-13 bluepill: Added RF decoder skeleton
2018-01-13 bluepill: Added stm32goodies to the project
2018-01-14 bluepill: Singleton<> moved to st32goodies
2018-01-15 bluepill: RF decoder working
2018-01-16 bluepill: RFDecoder: moved interrupt enablement to a separate Init() to avoid singleton initialization problem (get rid of SafeSingletonInitializer<> usage).
2018-01-16 bluepill: added SPI SD BSP and demo code
2018-01-18 DbgUsart stream operators
2018-01-18 hardware/stm32: bluepill schematics && PCB progress
2018-01-18 bluepill: Added SdFile, Loop detector inputs, USART3 for ESP-01
2018-01-19 bluepill: PCB 0.9
2018-01-20 bluepill PCB: SD Card socket turned around
2018-01-23 I2cEEPROM
2018-01-27 I2cMaster functions epect void* buffer pointers
2018-01-27 DS3231 added
2018-01-27 DbgUsart supports receiving
2018-02-01 All hardware handlers are working
2018-02-04 gate433-stm32: database and i2cdb ported from atmel version pwmoutputs and smartlights are working MainLoop class introduced
2018-02-05 Added license for STM32 hardware
2018-02-08 Usart: Renamed to Usart from DbgUsart Passing references to interfaces instead of pointers Usart is no singleton anymore (to allow multiple instances) Init() eliminated Using char* for buffers instea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
2018-02-08 strutil: Typo fix & resolve char signedness issue in getintparam()
2018-02-08 i2ceeprom: NeedPoll() bugfix
2018-02-08 SDFile: Open mode enum refactor, Size() implementation
2018-02-08 gate433-stm32: ITick.h->tick.h rename
2018-02-08 gate433-stm32: serial command line processing
2018-02-08 gate433-stm32: rename files to lowercase
2018-02-13 gate433-stm32: SD log writer added
2018-02-13 gate433-stm32: incoming codes are logged to SD SD log can be dumped to serial
2018-02-20 strutil: scalar to string function will render exact count of digits ds3231: number of year digits can be passed for date to string conversion
2018-02-20 gate433-stm32: almost there (need to implement Mainloop::Authorize)
2018-02-27 usart: functions returning numbers of characters sent now return size_t
2018-03-03 eliminating warnings (missing virtual destructor)
2018-03-03 gate433-stm32: UART: UART1 speed back to 115200, UART3 activated and handled the same as UART1 Timer initialization in main.c to shorten full power period for all lights on boot gt (Get Temperature) 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
2018-03-07 stm32 board test: added stm32goodies
2018-03-08 bluepill commandprocessor: new logic to handle renge for CS, handlers commented (function) sdlogwriter: const correctness, log queue mainloop: log if usart::Receive fails, log queue support
2018-03-10 bluepill: Opening and closing the gate
2018-03-16 Bluepill: Change rotary encoder button line to EXTI Decrease interrupt priority of everything except I2C
2018-03-17 i2clcd: removed inline from private finctions, added one char Print
2018-03-17 Bluepill: SHUFFLE.TXT handling
2018-03-18 File name CamelCasing
2018-03-18 bluepill: followup for Stm32Goodues changes (file/function renames)
2018-03-25 bluepill: transit timeout fix
2018-04-16 Added FreeCAD model of the case for STM32 version
2018-04-17 Config stuff
2018-04-17 More descriptive command names
2018-04-18 bluepill: Getting rid of designated initializers which will be standardized only in c++20
